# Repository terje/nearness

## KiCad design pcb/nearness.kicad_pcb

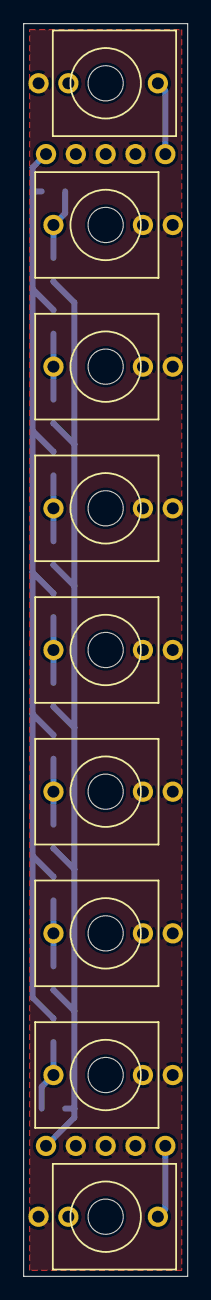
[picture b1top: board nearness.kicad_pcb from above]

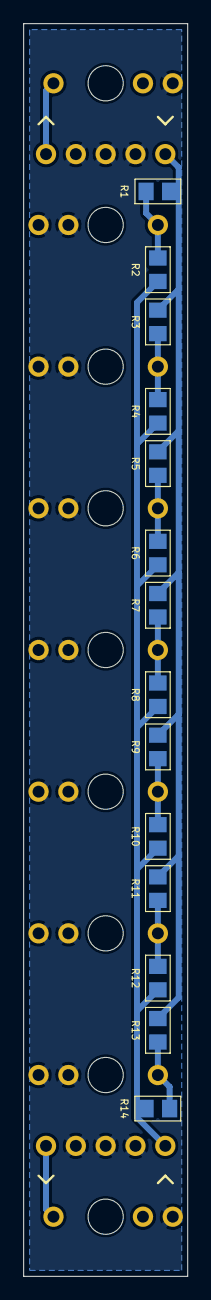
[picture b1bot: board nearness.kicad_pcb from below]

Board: 2 copper layers, 14.0 x 106.7 mm, 25 parts (14 on the bottom side), 12 nets.

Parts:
J1, J2, J3, J4, J5, J6, J7, J8, J9: PJ301M12
P1, P2: CONN_01X05; Pin_1x5
R1, R14: 100k; 0805
R2, R13: 1M67; 0805
R3, R12: 103k; 0805
R4, R11: 439k; 0805
R5, R10: 113k; 0805
R6, R9: 215k; 0805
R7, R8: 141k; 0805

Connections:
GND: J1.1, J2.1, J2.2, J3.1, J3.2, J4.1, J4.2, J5.1, J5.2, J6.1, J6.2, J7.1, J7.2, J8.1, J8.2, J9.1, P1.2, P1.3, P1.4, P2.2, P2.3, P2.4
unnamed: J1.3, P1.5
unnamed: J2.3, R1.1, R2.1
unnamed: J3.3, R3.1, R4.1
unnamed: J4.3, R5.1, R6.1
unnamed: J5.3, R7.1, R8.1
unnamed: J6.3, R9.1, R10.1
unnamed: J7.3, R11.1, R12.1
unnamed: J8.3, R13.1, R14.1
unnamed: J9.3, P2.5
unnamed: P1.1, R1.2, R3.2, R5.2, R7.2, R9.2, R11.2, R13.2
unnamed: P2.1, R2.2, R4.2, R6.2, R8.2, R10.2, R12.2, R14.2

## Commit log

2019-08-01 Updated symbols and silkscreen
